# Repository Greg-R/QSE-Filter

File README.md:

# QSE-Filter Version 1.0

This is the PCB for the QSE-Filter module for the T41 "Software Defined Transceiver".
The PCB was designed using the open-source design tool Kicad 8.

The primary documentation for the T41 is the book "Digital Signal Processing and Software Defined Radio:
Theory and Construction of the T41-EP Software Defined Transceiver" by Albert Peter and Jack Purdum.
The book is available here:

<https://www.amazon.com/Digital-Signal-Processing-Software-Defined/dp/B0D25FV48C>

The goal of the QSE-Filter is to improve T41 transmitter fidelity.  Without using
this filter, the transmit output will contain spurious energy.  Using this simple filter
will resolve this problem.  The QSE-Filter module is designed to be the simplest
and lowest cost circuit to resolve this specific spurious energy problem.

The QSE-Filter is inserted between the output of the QSE module and the input of the
Power Amplifier.

Gerber files for PCB fabrication are included in the gerbers folder.
A PDF of the schematic (QSE-Filter.pdf) is included for quick viewing of the circuit design.

A look at the schematic:

<https://github.com/Greg-R/QSE-Filter/blob/main/QSE-Filter.pdf>

## Video Illustration of the Spurious Problem

This video shows why it is necessary to have a filter on the output of the QSE:

<https://drive.google.com/file/d/18EVahQOBdGZIAjiurM7DPEM1uzlL1K75/view?usp=drive_link>

### Hardware Modifications

A new ribbon cable is required.  The original T41 has a 10-wire cable which connects the Main board module to the Low-Pass
Filter module.  Since the QSE-Filter shares the same control signals, a new ribbon cable is required which routes from the
Main board to the QSE-Filter, and then to the Low-Pass module.  This type of cable is very easy to build and can be
completed in five minutes or less.

A wire must be added to the Main board to supply 3.3 volts.  This wire should be soldered to the back side of the Main
board from pin 8 of the "Bands" connector to a convenient source of 3.3 volts.  Looking at my modified Main board:

<https://drive.google.com/file/d/1hGLFVzCbjHw2UNAi1ffdGSL7jEQ02EJ3/view?usp=drive_link>

The green wire in the upper right area of the Main board routes 3.3 volts to the QSE-Filter via the ribbon cable.

There is no modification required to the software.

### PCB Layout

The PCB layout was completed using Kicad version 8.  This is an open-source tool, unlike the "Dip Trace" commercial product used
to design the V010 and other T41 boards.

The prototype PCBs were fabricated by PCBWay at a cost of US$1.00 each.  Shipping was about US$25.00 for quantity 5 boards.

## Bill Of Material (BOM)

A public Digikey BOM is here:

<https://www.digikey.com/en/mylists/list/BP824NCB5P>

The toroids are not included in the above BOM.  The T-37-6 (quantity 6) and T-37-17 (quantity 4) may be ordered from:

<https://kitsandparts.com/>

## Build Tips

In general, QSE-Filter is easy to build if you have experience with surface-mount components.  There are a few items to be aware of
to avoid build errors.

### SOT Devices

This circuit uses a lot of SOT devices!  These are generally well behaved when using a hot-air soldering station.  Be careful to not
use too much solder on the pads.  I had one short-circuit underneath one of the switches which caused high filter loss.  A little
bit of probing with a DVM revealed the short, and once the short was cleared the circuit worked as expected.

### Toroids

This is what I consider the most difficult part of building the filter.  Toroid winding!
The toroid part numbers, wire gauge, and number of turns are shown on the schematic.

Try to space the windings evenly around the circumference of the toroid.  However, the will be a gap in the windings
at the wire ends.

The toroids are "surface mounted", meaning that there is a rectangular pad for soldering the wire end.  I find this much
easier to deal with than using through-holes, as soldering and re-soldering is much easier.  Why resoldering?  Because
it may be necessary to add or remove a turn to get the frequency response lined up just right.  Hopefully not, however,
there are tolerances associated with both the capacitors and the toroids.  The inductance will be a function of the toroid
permeability, the number of turns, and also how you wound it.  The frequency responses of the filters are designed to have
margin, so hopefully all will line up and the frequency response of the filters will achieve the goal of a clean transmit
spectrum.

I have recommended using AWG#28 for the 80, 40, and 20 meter coils, and AWG#27 for the 15 and 10 meter coils.
However, AWG#27 will probably work for all of the coils.  I have not tried this yet.

### 3D Printed Bracket

The QSE Filter uses a custom 3D printed bracket.  I have a repository with many files for T41 parts including the QSE Filter bracket:

<https://github.com/Greg-R/SDT_Case_KF5N>

### Bottom Side Parts

There are many parts on the bottom side.  These should be soldered after the top-side SMDs.  I was able to use a hot air gun without any of the top-side components desoldering.

Solder the 16 pin connector and the SMA connectors last.

### SMA Connectors

Take a good look at the placement of the board in your T41 radio.  You will want the SMA connectors of the QSE-Filter in the orientation for
easy coaxial cable routing.  0 or 90 degree connectors are available (90 degree parts are on the BOM).  Also, you may choose to put the SMAs on one side or the other for optimal cable routing.

### High Resolution Photos of QSE-Filter

Links to photos of a fully constructed QSE-Filter follow.

<https://drive.google.com/file/d/1yyc1hCo5w5VuUIPOOLpDOkUyore53iXK/view?usp=sharing>

<https://drive.google.com/file/d/1FSENao2-BARYMb8nm4-y8Q7-AhVFKQNp/view?usp=sharing>

## Example Measured Filter Response 10 Meters

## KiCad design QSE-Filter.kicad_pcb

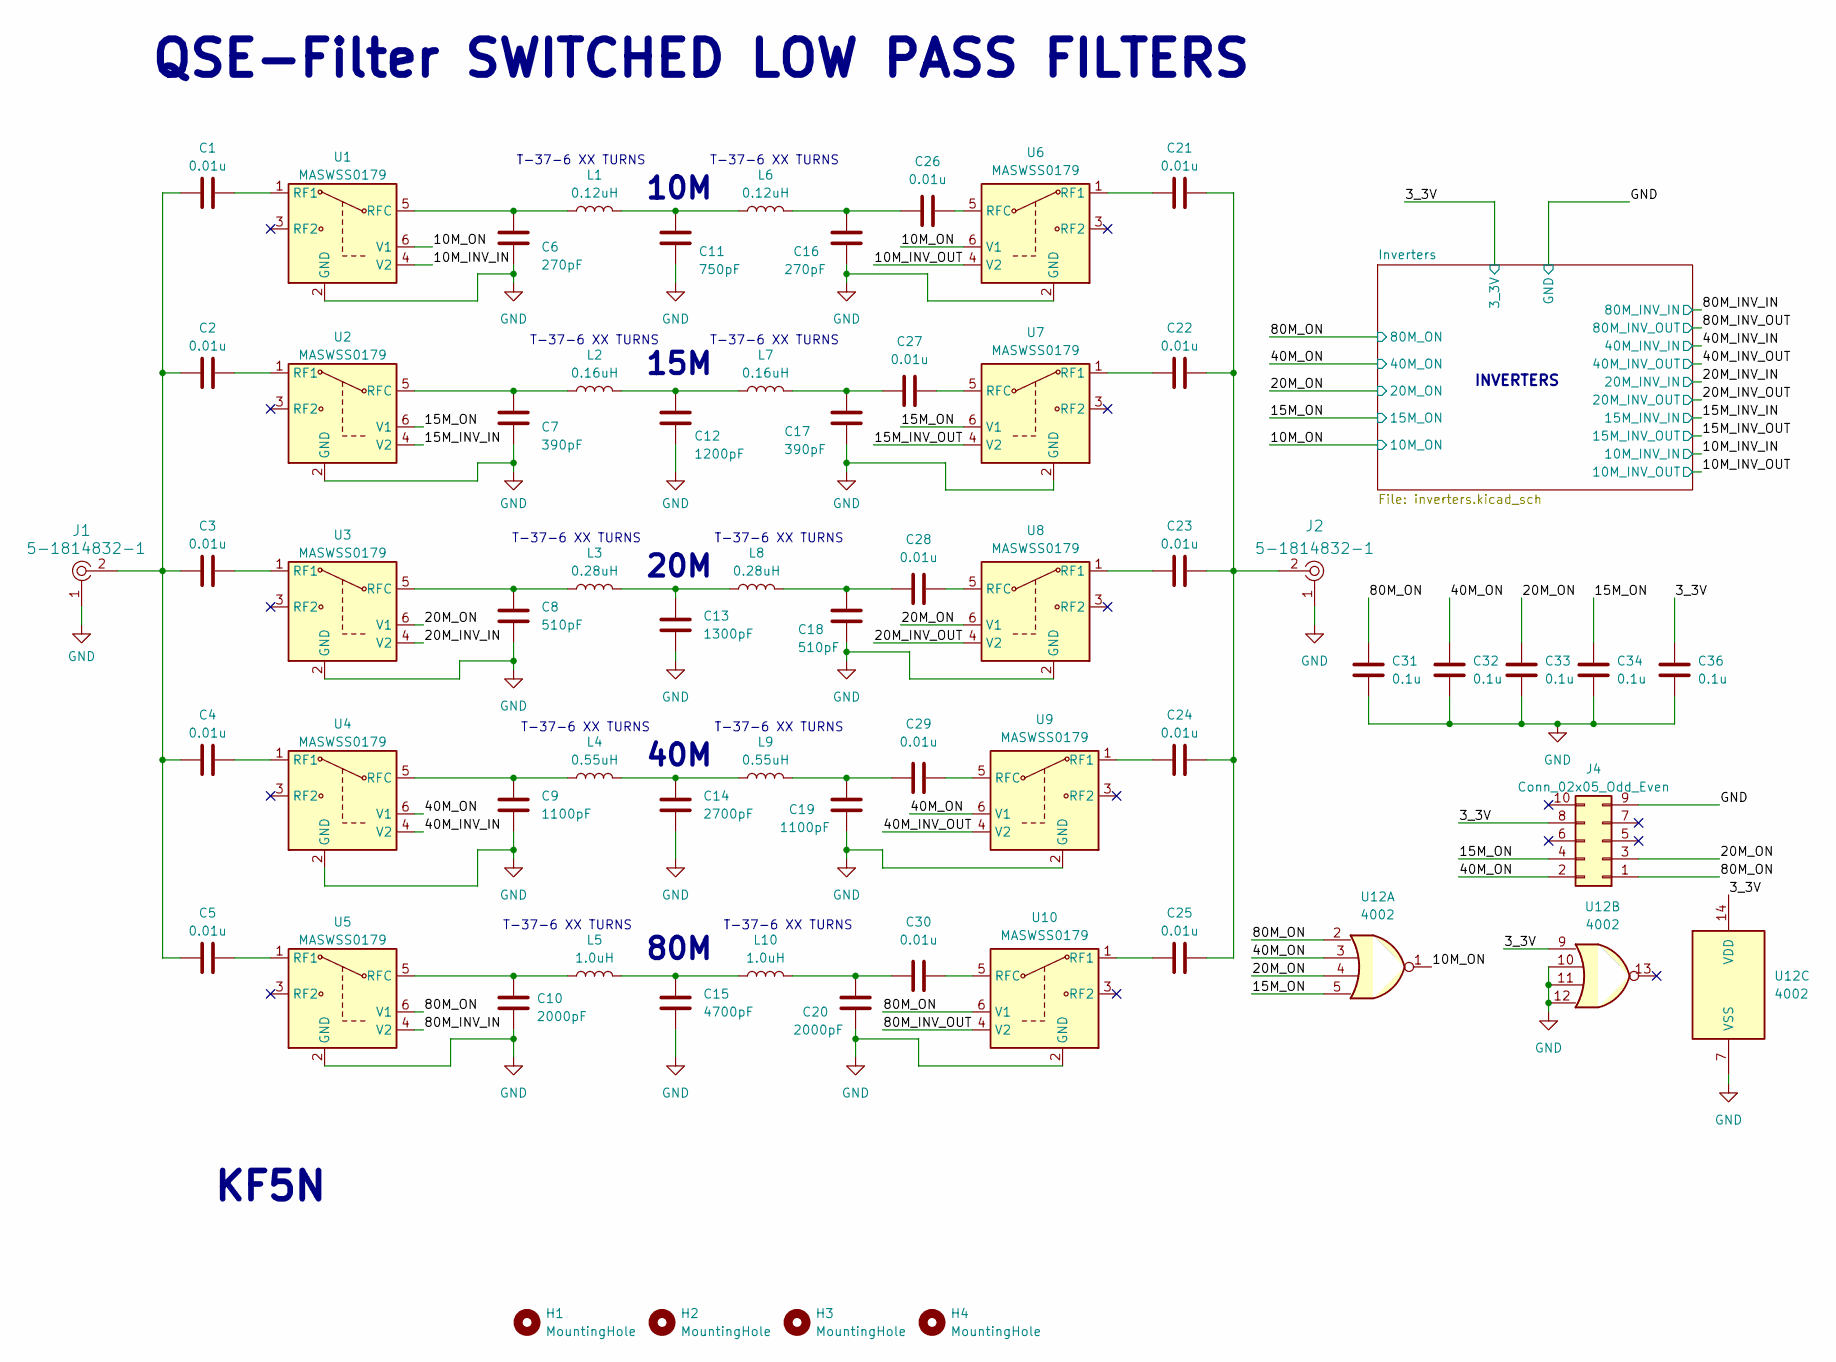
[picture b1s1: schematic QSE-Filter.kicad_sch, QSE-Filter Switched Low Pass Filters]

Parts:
C1, C2, C3, C4, C5, C21, C22, C23, C24, C25, C26, C27, C28, C29, C30: 0.01u; C_1206_3216Metric
C6, C16: 270pF; C_1206_3216Metric
C7, C17: 390pF; C_1206_3216Metric
C8, C18: 510pF; C_1206_3216Metric
C9, C19: 1100pF; C_1206_3216Metric
C10, C20: 2000pF; C_1206_3216Metric
C11: 750pF; C_1206_3216Metric
C12: 1200pF; C_1206_3216Metric
C13: 1300pF; C_1206_3216Metric
C14: 2700pF; C_1206_3216Metric
C15: 4700pF; C_1206_3216Metric
C31, C32, C33, C34, C36: 0.1u; C_1206_3216Metric
H1, H2, H3, H4: MountingHole; MountingHole_3.2mm_M3
J1, J2: 5-1814832-1; RF_SMA_Vertical_5-1814832-1; MPN 5-1814832-1; Digi-Key_PN A97594-ND
J4: Conn_02x05_Odd_Even; IDC-Header_2x05_P2.54mm_Vertical
L1, L6: 0.12uH; Toroid_SMD
L2, L7: 0.16uH; Toroid_SMD
L3, L8: 0.28uH; Toroid_SMD
L4, L9: 0.55uH; Toroid_SMD
L5, L10: 1.0uH; Toroid_SMD
U1, U2, U3, U4, U5, U6, U7, U8, U9, U10: MASWSS0179; SOT-23-6
U12: 4002; SOIC-14_3.9x8.7mm_P1.27mm

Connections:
/3_3V: C36.2, J4.8, U12.9, U12.14 (VDD); also elsewhere on the board
/10M_INV_IN: U1.4 (V2); also elsewhere on the board
/10M_INV_OUT: U6.4 (V2); also elsewhere on the board
/10M_ON: U1.6 (V1), U6.6 (V1), U12.1; also elsewhere on the board
/15M_INV_IN: U2.4 (V2); also elsewhere on the board
/15M_INV_OUT: U7.4 (V2); also elsewhere on the board
/15M_ON: C34.2, J4.4, U2.6 (V1), U7.6 (V1), U12.5; also elsewhere on the board
/20M_INV_IN: U3.4 (V2); also elsewhere on the board
/20M_INV_OUT: U8.4 (V2); also elsewhere on the board
/20M_ON: C33.2, J4.3, U3.6 (V1), U8.6 (V1), U12.4; also elsewhere on the board
/40M_INV_IN: U4.4 (V2); also elsewhere on the board
/40M_INV_OUT: U9.4 (V2); also elsewhere on the board
/40M_ON: C32.2, J4.2, U4.6 (V1), U9.6 (V1), U12.3; also elsewhere on the board
/80M_INV_IN: U5.4 (V2); also elsewhere on the board
/80M_INV_OUT: U10.4 (V2); also elsewhere on the board
/80M_ON: C31.2, J4.1, U5.6 (V1), U10.6 (V1), U12.2; also elsewhere on the board
GND: C6.2, C7.2, C8.2, C9.2, C10.2, C11.2, C12.2, C13.2, C14.2, C15.2, C16.2, C17.2, C18.2, C19.2, C20.2, C31.1, C32.1, C33.1, C34.1, C36.1, J1.1, J2.1, J4.9, U1.2 (GND), U2.2 (GND), U3.2 (GND), U4.2 (GND), U5.2 (GND), U6.2 (GND), U7.2 (GND), U8.2 (GND), U9.2 (GND), U10.2 (GND), U12.7 (VSS), U12.10, U12.11, U12.12; also elsewhere on the board
unnamed: C1.1, C2.1, C3.1, C4.1, C5.1, J1.2
unnamed: C11.1, L1.2, L6.1
unnamed: C12.1, L2.2, L7.1
unnamed: C13.1, L3.2, L8.1
unnamed: C14.1, L4.2, L9.1
unnamed: C15.1, L5.2, L10.1
unnamed: C16.1, C26.1, L6.2
unnamed: C17.1, C27.1, L7.2
unnamed: C18.1, C28.1, L8.2
unnamed: C19.1, C29.1, L9.2
unnamed: C20.1, C30.1, L10.2
unnamed: C21.2, C22.2, C23.2, C24.2, C25.2, J2.2
unnamed: C1.2, U1.1 (RF1)
unnamed: C6.1, L1.1, U1.5 (RFC)
unnamed: C2.2, U2.1 (RF1)
unnamed: C7.1, L2.1, U2.5 (RFC)
unnamed: C3.2, U3.1 (RF1)
unnamed: C8.1, L3.1, U3.5 (RFC)
unnamed: C4.2, U4.1 (RF1)
unnamed: C9.1, L4.1, U4.5 (RFC)
unnamed: C5.2, U5.1 (RF1)
unnamed: C10.1, L5.1, U5.5 (RFC)
unnamed: C21.1, U6.1 (RF1)
unnamed: C26.2, U6.5 (RFC)
unnamed: C22.1, U7.1 (RF1)
unnamed: C27.2, U7.5 (RFC)
unnamed: C23.1, U8.1 (RF1)
unnamed: C28.2, U8.5 (RFC)
unnamed: C24.1, U9.1 (RF1)
unnamed: C29.2, U9.5 (RFC)
unnamed: C25.1, U10.1 (RF1)
unnamed: C30.2, U10.5 (RFC)

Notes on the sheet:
T-37-6 XX TURNS
INVERTERS
40M
QSE-Filter SWITCHED LOW PASS FILTERS
15M
80M
20M
10M
KF5N

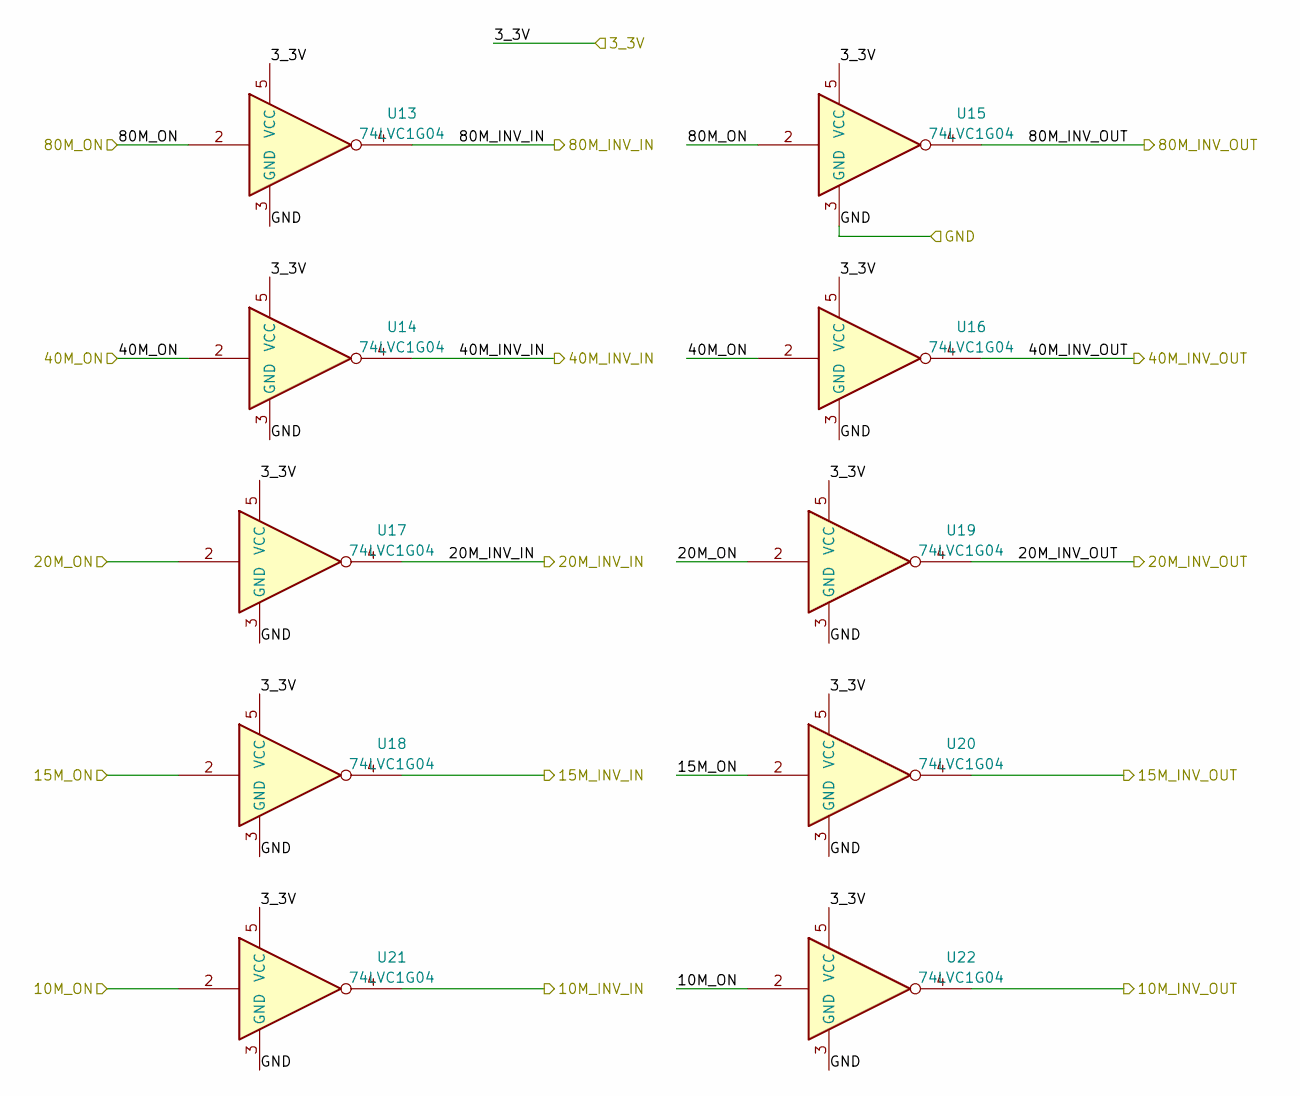
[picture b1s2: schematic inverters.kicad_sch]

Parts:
U13, U14, U15, U16, U17, U18, U19, U20, U21, U22: 74LVC1G04; SOT-353

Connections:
/3_3V: U13.5 (VCC), U14.5 (VCC), U15.5 (VCC), U16.5 (VCC), U17.5 (VCC), U18.5 (VCC), U19.5 (VCC), U20.5 (VCC), U21.5 (VCC), U22.5 (VCC); also elsewhere on the board
/10M_INV_IN: U21.4; also elsewhere on the board
/10M_INV_OUT: U22.4; also elsewhere on the board
/10M_ON: U21.2, U22.2; also elsewhere on the board
/15M_INV_IN: U18.4; also elsewhere on the board
/15M_INV_OUT: U20.4; also elsewhere on the board
/15M_ON: U18.2, U20.2; also elsewhere on the board
/20M_INV_IN: U17.4; also elsewhere on the board
/20M_INV_OUT: U19.4; also elsewhere on the board
/20M_ON: U17.2, U19.2; also elsewhere on the board
/40M_INV_IN: U14.4; also elsewhere on the board
/40M_INV_OUT: U16.4; also elsewhere on the board
/40M_ON: U14.2, U16.2; also elsewhere on the board
/80M_INV_IN: U13.4; also elsewhere on the board
/80M_INV_OUT: U15.4; also elsewhere on the board
/80M_ON: U13.2, U15.2; also elsewhere on the board
GND: U13.3 (GND), U14.3 (GND), U15.3 (GND), U16.3 (GND), U17.3 (GND), U18.3 (GND), U19.3 (GND), U20.3 (GND), U21.3 (GND), U22.3 (GND); also elsewhere on the board

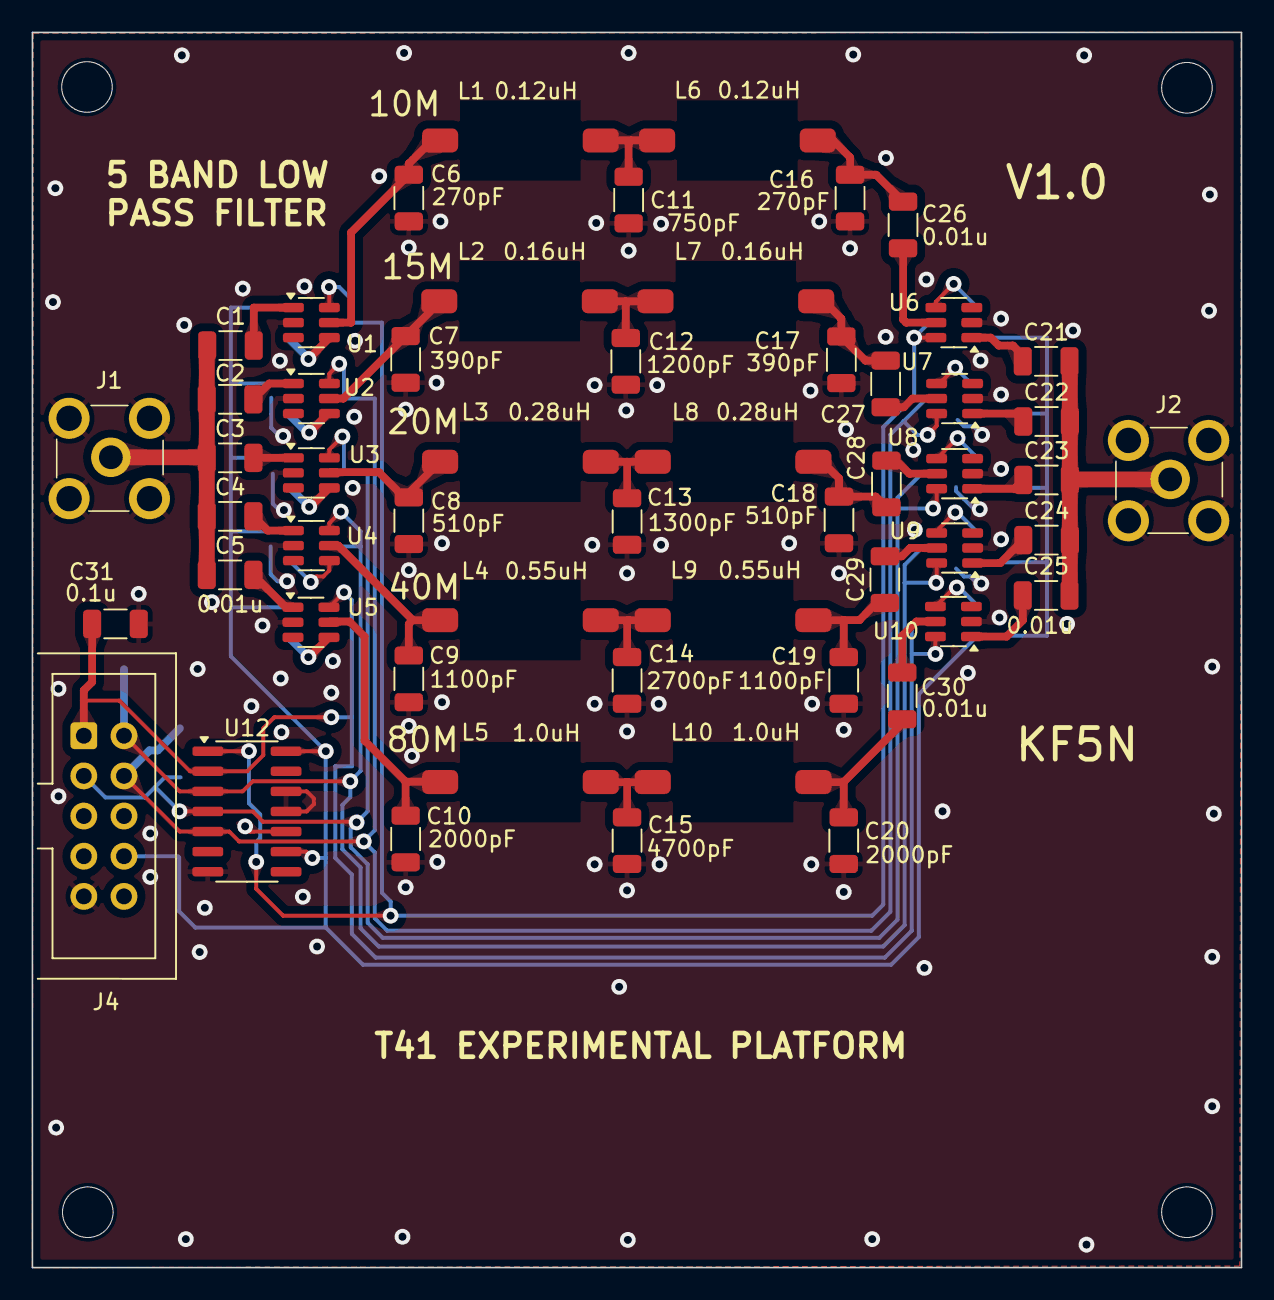
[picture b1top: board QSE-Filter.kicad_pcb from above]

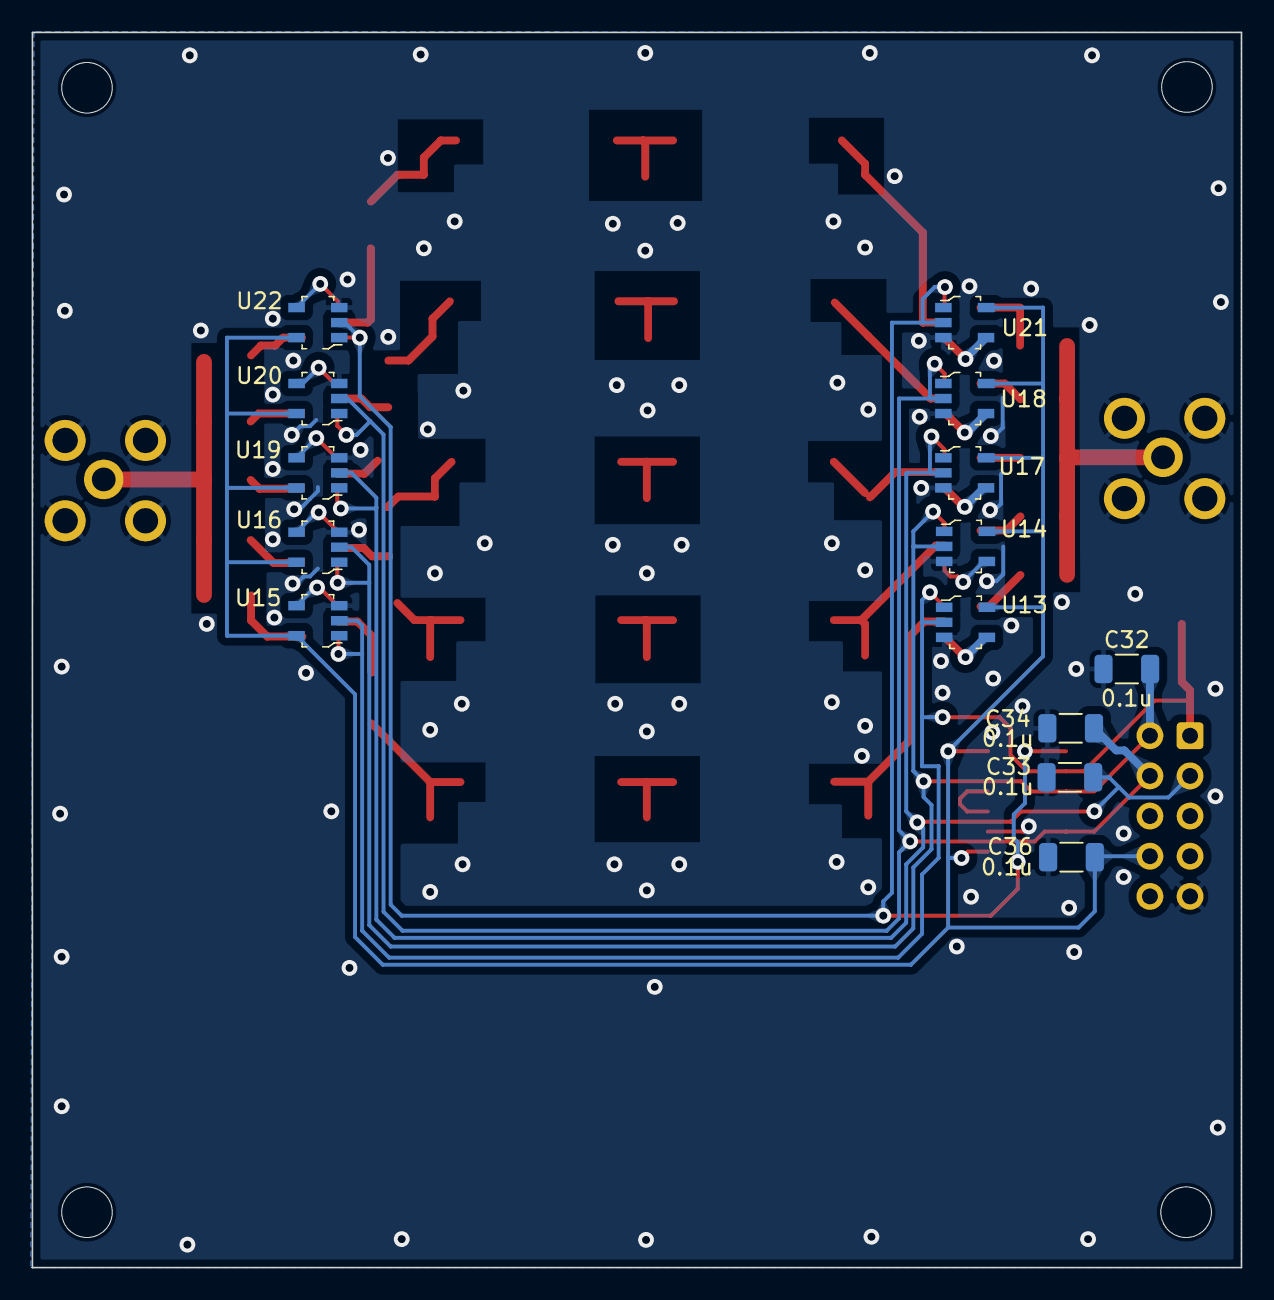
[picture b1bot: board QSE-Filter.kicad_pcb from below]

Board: 2 copper layers, 76.5 x 78.1 mm, 73 parts (14 on the bottom side), 49 nets.

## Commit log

2024-05-09 Initial commit.
2024-05-09 Further edits.
2024-05-09 Updated link to image.
2024-05-09 Try again to get image correct.
2024-05-09 Updated schematic with toroid winding information.
2024-05-09 Minor update to README.
2024-05-10 Added link to revised schematic.
2024-05-11 Added comment on wire added to Main board.
2024-06-20 Updated comment on bracket.
